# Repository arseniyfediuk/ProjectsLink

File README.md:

# ProjectsLink

A collection of my electronics and software engineering projects.

1\. \[Huawei STC 2026 – Digital Energy]

A hybrid digital energy system (solar panels, gas CHP generator, and battery storage) developed for the Huawei Student Tech Conference 2026. Includes the technical architecture overview and English pitching materials that took our 3-member engineering team to the national semifinals in Kyiv.

2\. \[AC Zero-Cross Detector]

Hardware design, calculation, and documentation for a solid-state AC power-switching device. This project features a zero-crossing detector using PC814 optocouplers to safely monitor 230V/50Hz mains and generate precise synchronization pulses for microcontroller phase control. Includes circuit calculations, EasyEDA PCB routing, and real oscilloscope test results.

3\. \[KiCad Laboratory Works]

A collection of educational PCB design projects completed during my university studies. Demonstrates the full hardware development cycle: schematic capture (Eeschema), manual topological trace routing (Pcbnew), DRC/ERC checks, component specification, and 3D board visualization.

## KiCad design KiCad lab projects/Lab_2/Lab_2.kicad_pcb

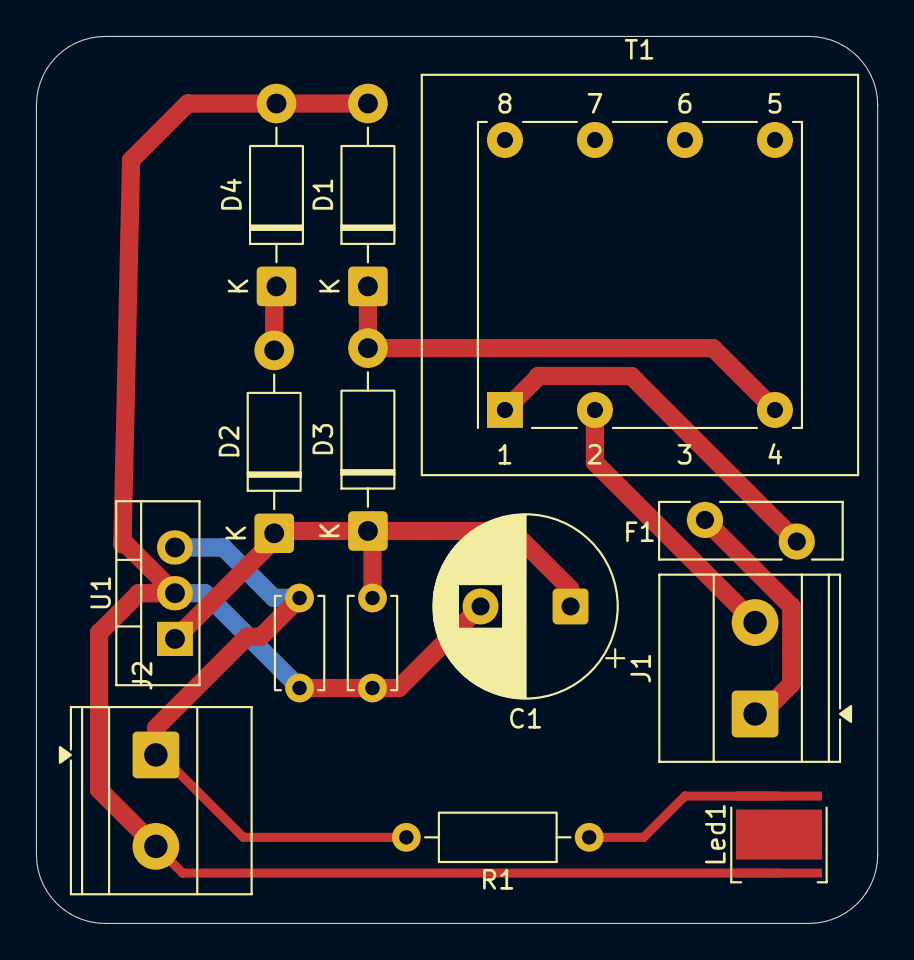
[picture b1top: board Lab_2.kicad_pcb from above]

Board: 2 copper layers, 46.7 x 49.3 mm, 14 parts (0 on the bottom side), 9 nets.

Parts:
C1: 1000u; CP_Radial_D10.0mm_P5.00mm
C2: 330n; C_Disc_D5.0mm_W2.5mm_P5.00mm
C4: 100n; C_Disc_D5.0mm_W2.5mm_P5.00mm
D1, D2, D3, D4: 1N4007; D_DO-41_SOD81_P10.16mm_Horizontal
F1: Fuse_Small; Fuse_Bourns_MF-RHT400
J1, J2: Screw_Terminal_01x02; TerminalBlock_Phoenix_MKDS-1,5-2-5.08_1x02_P5.08mm_Horizont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
Led1: LED; LED_Cree-XHP50_3V_HighDensity
R1: 330; R_Axial_DIN0207_L6.3mm_D2.5mm_P10.16mm_Horizontal
T1: Transformer_1P_1S; Transformer_Breve_TEZ-22x24
U1: LM78M05_TO220; TO-220-3_Vertical

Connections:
GND: C1.2, C2.2, C4.2, D1.2 (A), D4.2 (A), J2.2, Led1.1 (K), U1.2 (GND)
unnamed: D1.1 (K), D3.2 (A), T1.4 (SB)
unnamed: D2.2 (A), D4.1 (K)
unnamed: C1.1, C2.1, D2.1 (K), D3.1 (K), U1.1 (VI)
unnamed: F1.2, J1.1
unnamed: J1.2, T1.2 (AB)
unnamed: C4.1, J2.1, R1.2, U1.3 (VO)
unnamed: Led1.2 (A), R1.1
unnamed: F1.1, T1.1 (AA)

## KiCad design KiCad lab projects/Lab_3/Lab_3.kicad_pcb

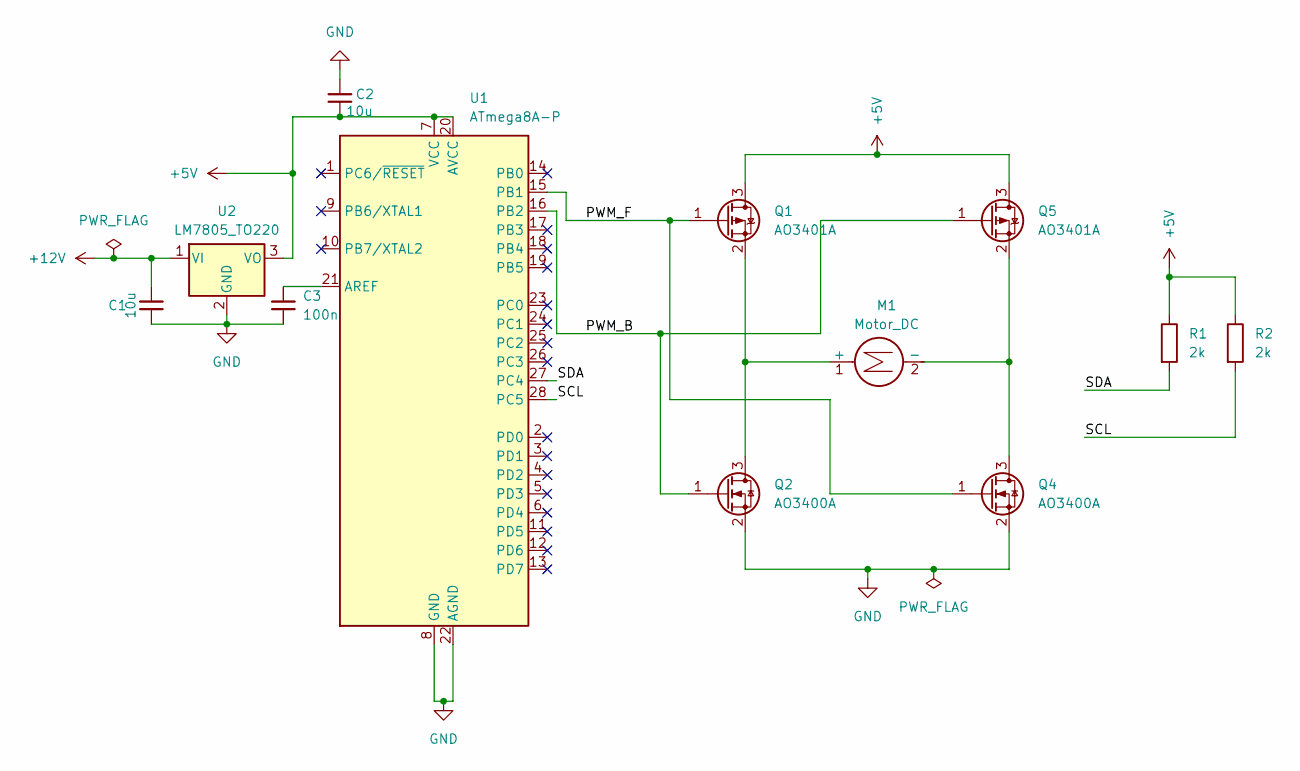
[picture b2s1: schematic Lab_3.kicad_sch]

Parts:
C1, C2: 10u; C_1206_3216Metric
C3: 100n; C_0805_2012Metric
M1: Motor_DC; TerminalBlock_Phoenix_MKDS-1,5-2-5.08_1x02_P5.08mm_Horizont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
Q1, Q5: AO3401A; SOT-23
Q2, Q4: AO3400A; SOT-23
R1, R2: 2k; R_0805_2012Metric
U1: ATmega8A-P; TQFP-32_7x7mm_P0.8mm
U2: LM7805_TO220; TO-220-3_Vertical

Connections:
+5V: C2.1, Q1.3 (D), Q5.3 (D), R1.1, R2.1, U1.7 (VCC), U1.20 (AVCC), U2.3 (VO)
+12V: C1.2, U2.1 (VI)
/PWM_B: Q2.1 (G), Q5.1 (G), U1.16 (PB2)
/PWM_F: Q1.1 (G), Q4.1 (G), U1.15 (PB1)
/SCL: R2.2, U1.28 (PC5)
/SDA: R1.2, U1.27 (PC4)
GND: C1.1, C2.2, C3.2, Q2.2 (S), Q4.2 (S), U1.8 (GND), U1.22 (AGND), U2.2 (GND)
unnamed: M1.1 (+), Q1.2 (S), Q2.3 (D)
unnamed: M1.2 (-), Q4.3 (D), Q5.2 (S)
unnamed: C3.1, U1.21 (AREF)

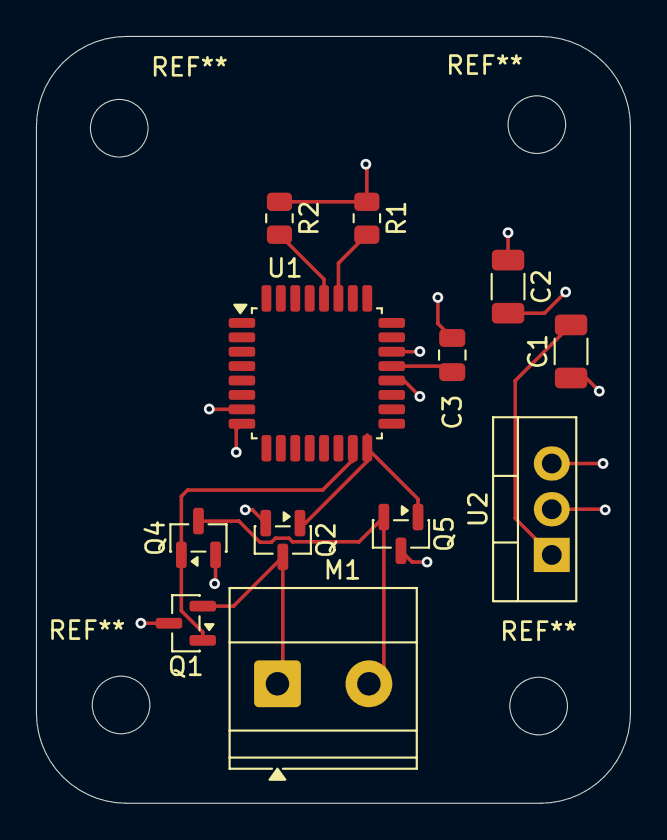
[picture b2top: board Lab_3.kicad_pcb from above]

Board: 4 copper layers, 33.0 x 42.6 mm, 12 parts (0 on the bottom side), 10 nets.

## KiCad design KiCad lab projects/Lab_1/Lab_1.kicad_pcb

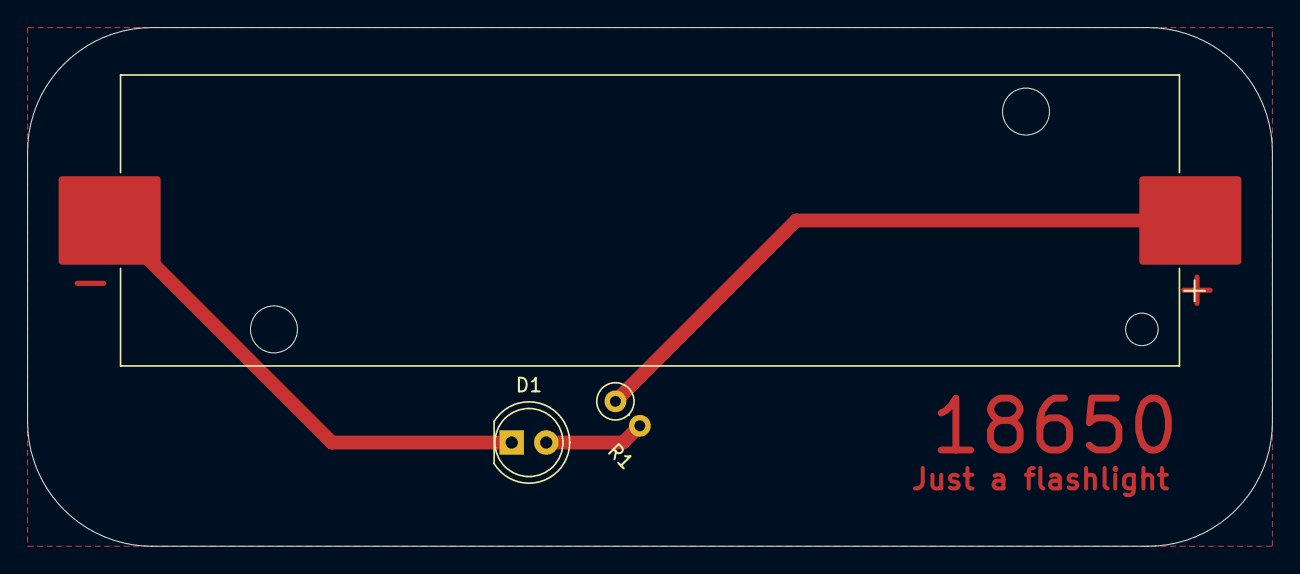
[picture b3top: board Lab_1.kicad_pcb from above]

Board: 2 copper layers, 91.4 x 38.1 mm, 3 parts (0 on the bottom side), 3 nets.

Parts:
BT1: Battery; BatteryHolder_Keystone_1042_1x18650
D1: LED; LED_D5.0mm
R1: 310; R_Axial_DIN0207_L6.3mm_D2.5mm_P2.54mm_Vertical

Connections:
unnamed: BT1.1 (+), R1.1
unnamed: BT1.2 (-), D1.1 (K)
unnamed: D1.2 (A), R1.2
